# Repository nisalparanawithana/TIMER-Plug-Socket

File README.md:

# TIMER-Plug-Socket
This is my 3rd year group Project of Engineering Product Design.
An electirc plug socket for domestic users with a time control setting
Enable the abilty to reduce energy wastage & time wastage
Flexible to assemble with the domestic electrical installation system

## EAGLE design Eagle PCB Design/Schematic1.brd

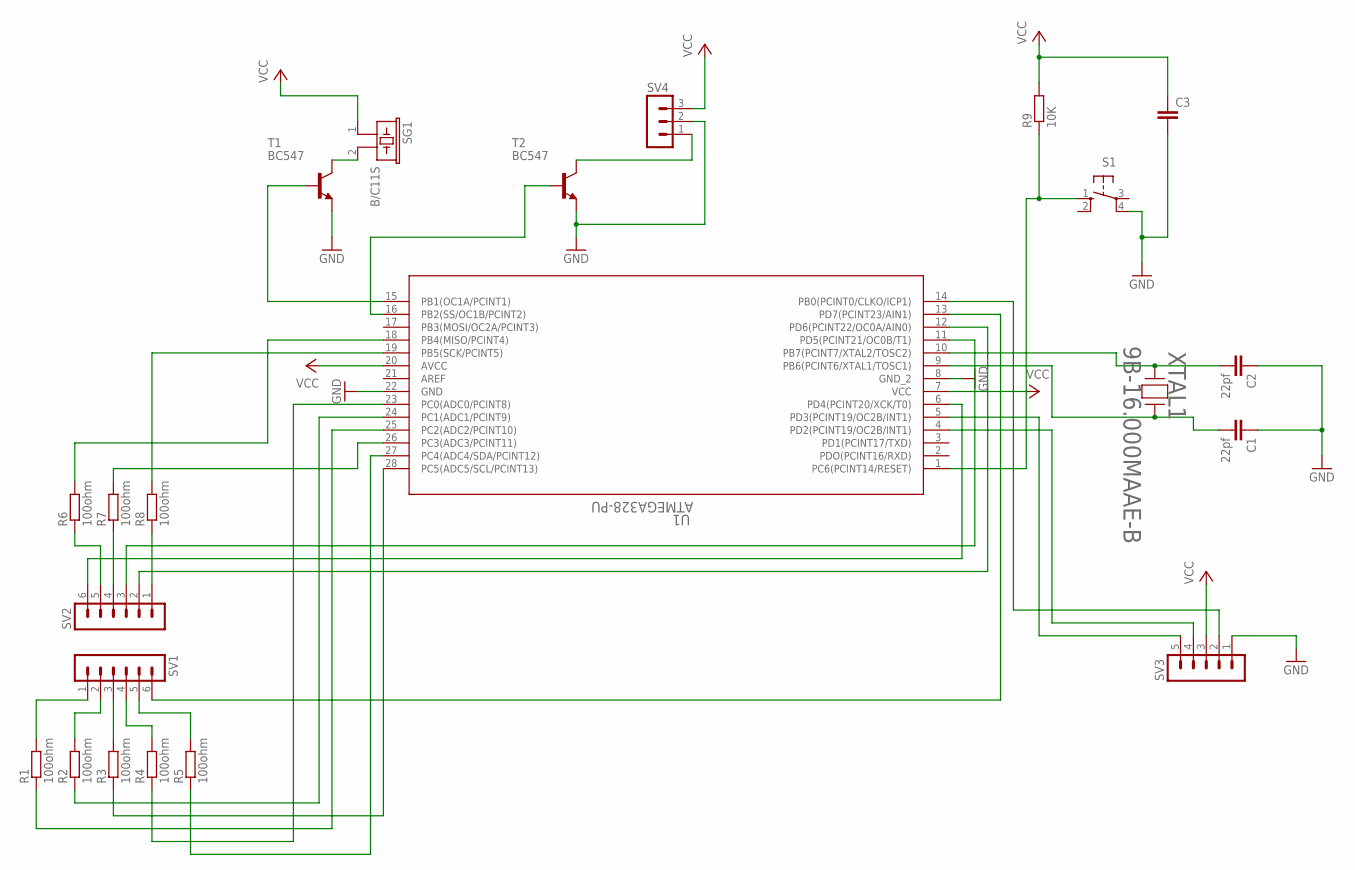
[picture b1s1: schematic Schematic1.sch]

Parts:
C1, C2: 22pf; C2.5-3
C3: C5/3; C5B3
R1, R2, R3, R4, R5, R6, R7, R8: 100ohm; 0204/7
R9: 10K; 0204/7
S1: 10-XX; B3F-10XX
SG1: B/C11S
SV1, SV2: MA06-1
SV3: MA05-1
SV4: MA03-1
T1, T2: BC547; TO92
U1: ATMEGA328-PU; 28P3_SPDIP28_SP_MCH
XTAL1: 9B-16.000MAAE-B; 9B-16.000MAAE-B_TXC

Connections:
GND: C1.1, C2.1, C3.2, S1.4 (P1), SV3.1, SV4.2, T1.1 (E), T2.1 (E), U1.8 (GND_2), U1.22 (GND)
unnamed: R1.2, SV1.1
unnamed: R1.1, U1.25 (PC2(ADC2/PCINT10))
unnamed: R2.2, SV1.2
unnamed: R3.2, SV1.3
unnamed: R4.2, SV1.4
unnamed: R2.1, U1.24 (PC1(ADC1/PCINT9))
unnamed: SV1.6, U1.13 (PD7(PCINT23/AIN1))
unnamed: R4.1, U1.23 (PC0(ADC0/PCINT8))
unnamed: R5.2, SV1.5
unnamed: R5.1, U1.27 (PC4(ADC4/SDA/PCINT12))
unnamed: R8.1, SV2.1
unnamed: R8.2, U1.19 (PB5(SCK/PCINT5))
unnamed: SV2.2, U1.12 (PD6(PCINT22/OC0A/AIN0))
unnamed: SV2.3, U1.11 (PD5(PCINT21/OC0B/T1))
unnamed: R7.1, SV2.4
unnamed: R7.2, U1.26 (PC3(ADC3/PCINT11))
unnamed: R6.1, SV2.5
unnamed: R6.2, U1.18 (PB4(MISO/PCINT4))
unnamed: SV2.6, U1.6 (PD4(PCINT20/XCK/T0))
unnamed: C1.2, U1.9 (PB6(PCINT6/XTAL1/TOSC1)), XTAL1.2
unnamed: C2.2, U1.10 (PB7(PCINT7/XTAL2/TOSC2)), XTAL1.1
unnamed: T1.2 (B), U1.15 (PB1(OC1A/PCINT1))
unnamed: SV3.2, SV3.5, U1.5 (PD3(PCINT19/OC2B/INT1)), U1.14 (PB0(PCINT0/CLKO/ICP1))
unnamed: SV3.4, U1.4 (PD2(PCINT19/OC2B/INT1))
unnamed: SG1.2, T1.3 (C)
unnamed: T2.2 (B), U1.16 (PB2(SS/OC1B/PCINT2))
unnamed: SV4.1, T2.3 (C)
unnamed: R9.1, S1.1 (S), U1.1 (PC6(PCINT14/RESET))
VCC: C3.1, R9.2, SG1.1, SV3.3, SV4.3, U1.7 (VCC), U1.20 (AVCC)

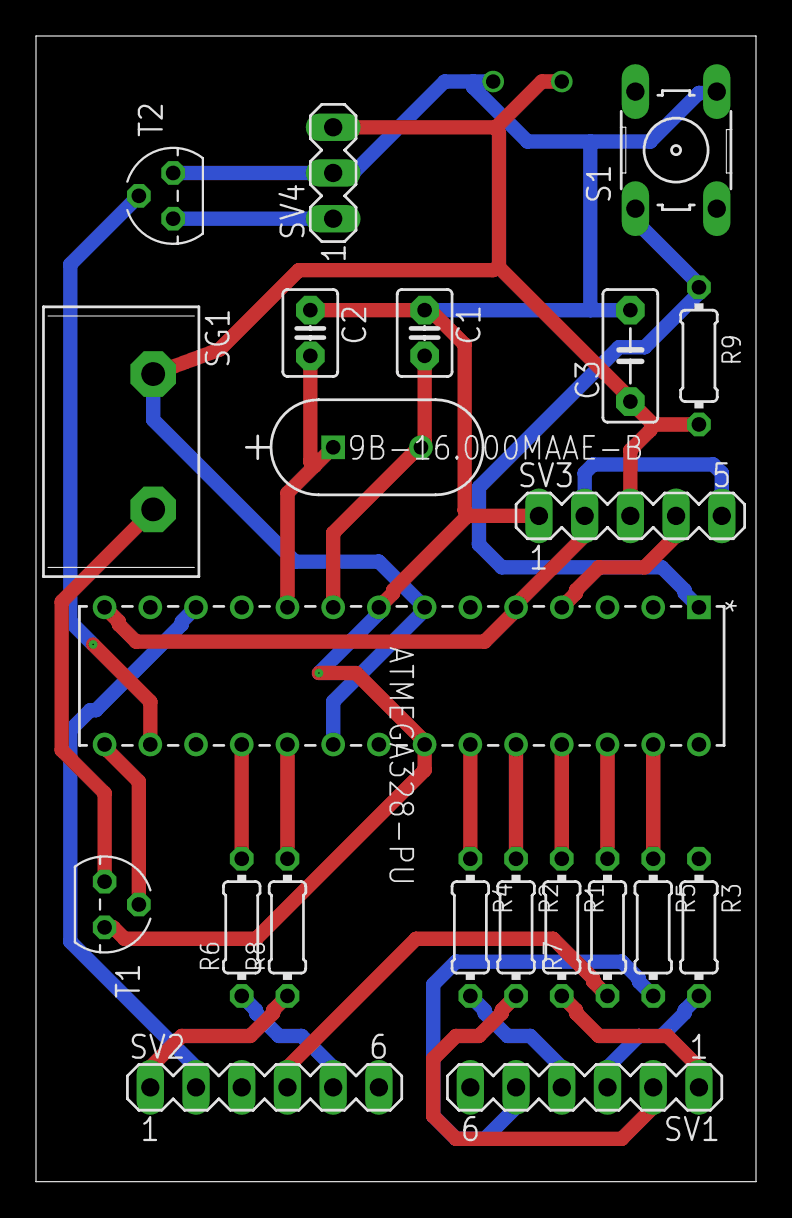
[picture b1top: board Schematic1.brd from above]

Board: 2 copper layers, 40.0 x 63.6 mm, 22 parts (0 on the bottom side), 30 nets.

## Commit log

2023-10-14 Add files via upload
    This is my 3rd year group project of Engineering Product Design. Under the project, we have designed an electric plug socket for the domestic users which can be controlled by a time control setting. 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

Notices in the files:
parts and their libraries:
COPYRIGHT: Copyright (C) 2023 Ultra Librarian. All rights reserved.
